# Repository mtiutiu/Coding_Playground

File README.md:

# Coding_Playground

Various coding projects and stuff.

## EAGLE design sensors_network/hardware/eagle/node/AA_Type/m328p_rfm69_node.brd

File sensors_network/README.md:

## MySensors Network 

#### System/RF24 MySensors Network overview

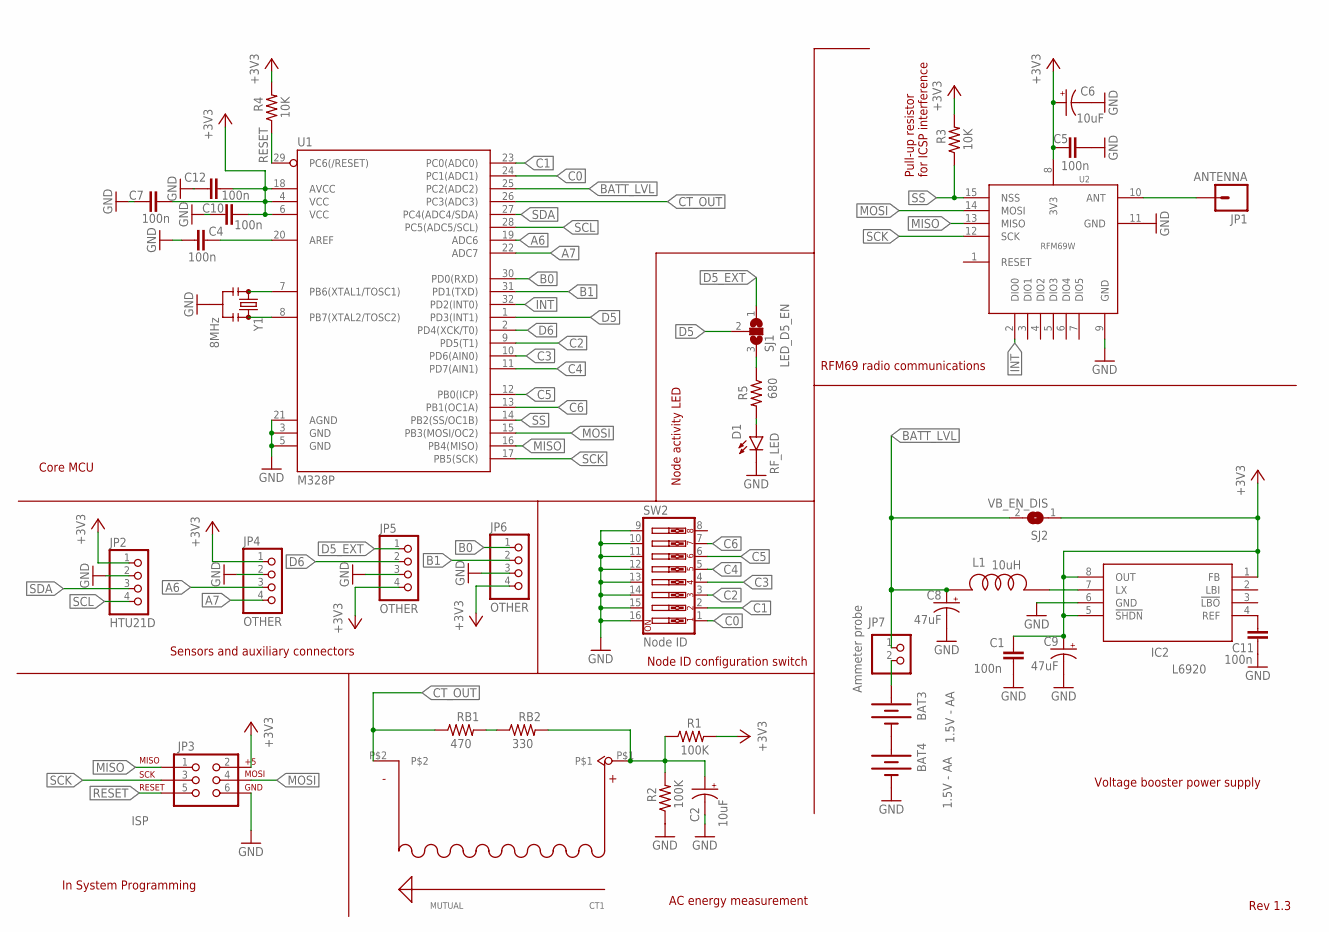
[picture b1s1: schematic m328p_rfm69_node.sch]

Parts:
BAT3, BAT4: 1.5V - AA; BATTERY-AA-KIT
C1, C4, C5, C7, C10, C11, C12: 100n; 0805
C2, C6: 10uF; EIA3528
C8, C9: 47uF; EIA3528
CT1: MUTUAL
D1: RF_LED; LED-0603
IC2: L6920; TSSOP8
JP1: ANTENNA; LUXEON-PAD
JP2: HTU21D; 1X04
JP3: ISP; 2X3-NS
JP4, JP5, JP6: OTHER; 1X04
JP7: Ammeter probe; 1X02
L1: 10uH; DLJ-4018
R1, R2: 100K; 0805
R3, R4: 10K; 0805
R5: 680; 0805
RB1: 470; 0805
RB2: 330; 0805
SJ1: LED_D5_EN; SJ_2
SJ2: VB_EN_DIS; SJ
SW2: Node ID; DIPSWITCH-08-50MIL
U1: M328P; TQFP32-08
U2: RFM69W
Y1: 8MHz; RESONATOR-SMD_MED

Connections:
+3V3: C1.1, C5.1, C6.A (+), C7.2, C9.A (+), C10.2, C12.2, IC2.1 (FB), IC2.5 (!SHDN), IC2.8 (OUT), JP2.1, JP3.2, JP4.1, JP5.4, JP6.4, R1.2, R3.2, R4.2, SJ2.1, U1.4 (VCC), U1.6 (VCC), U1.18 (AVCC), U2.8 (3V3)
A6: JP4.3, U1.19 (ADC6)
A7: JP4.4, U1.22 (ADC7)
B0: JP6.1, U1.30 (PD0(RXD))
B1: JP6.2, U1.31 (PD1(TXD))
BATT_LVL: C8.A (+), JP7.1, L1.P$2 (2), SJ2.2, U1.25 (PC2(ADC2))
C0: SW2.1, U1.24 (PC1(ADC1))
C1: SW2.2, U1.23 (PC0(ADC0))
C2: SW2.3, U1.9 (PD5(T1))
C3: SW2.4, U1.10 (PD6(AIN0))
C4: SW2.5, U1.11 (PD7(AIN1))
C5: SW2.6, U1.12 (PB0(ICP))
C6: SW2.7, U1.13 (PB1(OC1A))
CT_OUT: CT1.P$2, RB1.1, U1.26 (PC3(ADC3))
D5: SJ1.2, U1.1 (PD3(INT1))
D5_EXT: JP5.1, SJ1.1
D6: JP5.2, U1.2 (PD4(XCK/T0))
GND: BAT4.GND@1 (-), C1.2, C2.C (-), C4.1, C5.2, C6.C (-), C7.1, C8.C (-), C9.C (-), C10.1, C11.2, C12.1, D1.C, IC2.6 (GND), JP2.2, JP3.6, JP4.2, JP5.3, JP6.3, R2.1, SW2.9, SW2.10, SW2.11, SW2.12, SW2.13, SW2.14, SW2.15, SW2.16, U1.3 (GND), U1.5 (GND), U1.21 (AGND), U2.9 (GND), U2.11 (GND), Y1.2
INT: U1.32 (PD2(INT0)), U2.2 (DIO0)
MISO: JP3.1, U1.16 (PB4(MISO)), U2.13 (MISO)
MOSI: JP3.4, U1.15 (PB3(MOSI/OC2)), U2.14 (MOSI)
unnamed: IC2.7 (LX), L1.P$1 (1)
unnamed: D1.A, R5.2
unnamed: RB1.2, RB2.1
unnamed: C11.1, IC2.4 (REF)
unnamed: BAT3.PWR@1 (+), JP7.2
unnamed: U1.8 (PB7(XTAL2/TOSC2)), Y1.3
unnamed: BAT3.GND@1 (-), BAT4.PWR@1 (+)
unnamed: U1.7 (PB6(XTAL1/TOSC1)), Y1.1
unnamed: JP1.P$1, U2.10 (ANT)
unnamed: C2.A (+), CT1.P$1, R1.1, R2.2, RB2.2
unnamed: C4.2, U1.20 (AREF)
unnamed: R5.1, SJ1.3
RESET: JP3.5, R4.1, U1.29 (PC6(/RESET))
SCK: JP3.3, U1.17 (PB5(SCK)), U2.12 (SCK)
SCL: JP2.4, U1.28 (PC5(ADC5/SCL))
SDA: JP2.3, U1.27 (PC4(ADC4/SDA))
SS: R3.1, U1.14 (PB2(SS/OC1B)), U2.15 (NSS)

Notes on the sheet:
In System Programming
Sensors and auxiliary connectors
Core MCU
RFM69 radio communications
Voltage booster power supply
AC energy measurement
Pull-up resistor for ICSP interference
Node ID configuration switch
Node activity LED
Rev 1.3

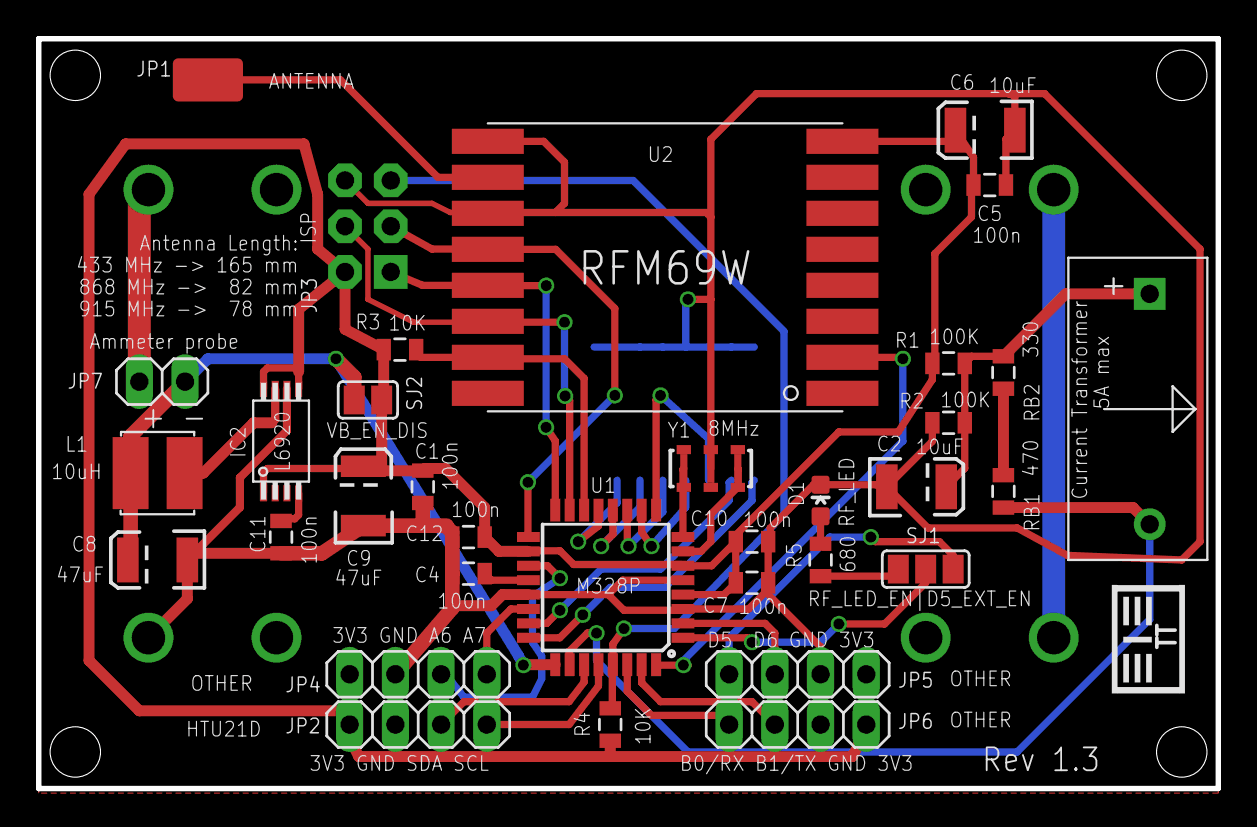
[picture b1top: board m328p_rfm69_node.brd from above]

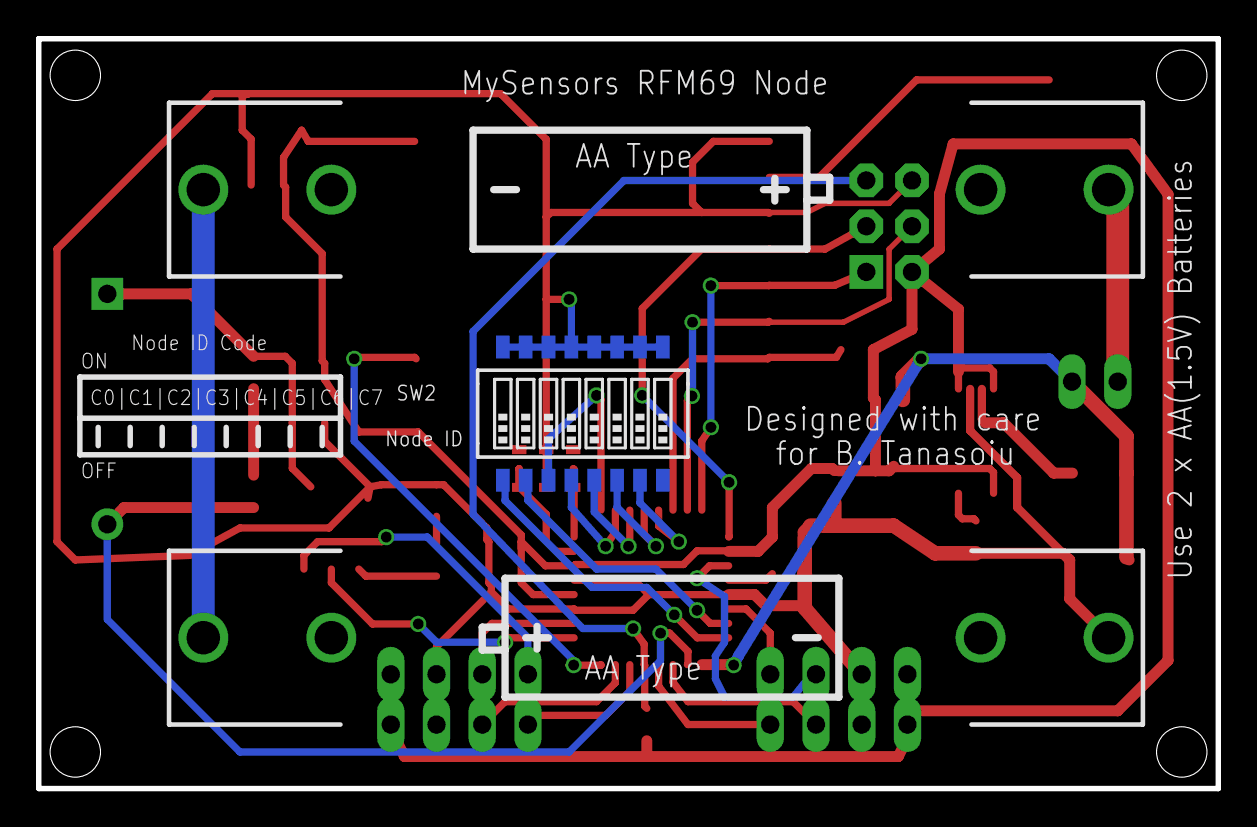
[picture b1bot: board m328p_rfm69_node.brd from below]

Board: 2 copper layers, 65.5 x 41.7 mm, 37 parts (3 on the bottom side), 38 nets.

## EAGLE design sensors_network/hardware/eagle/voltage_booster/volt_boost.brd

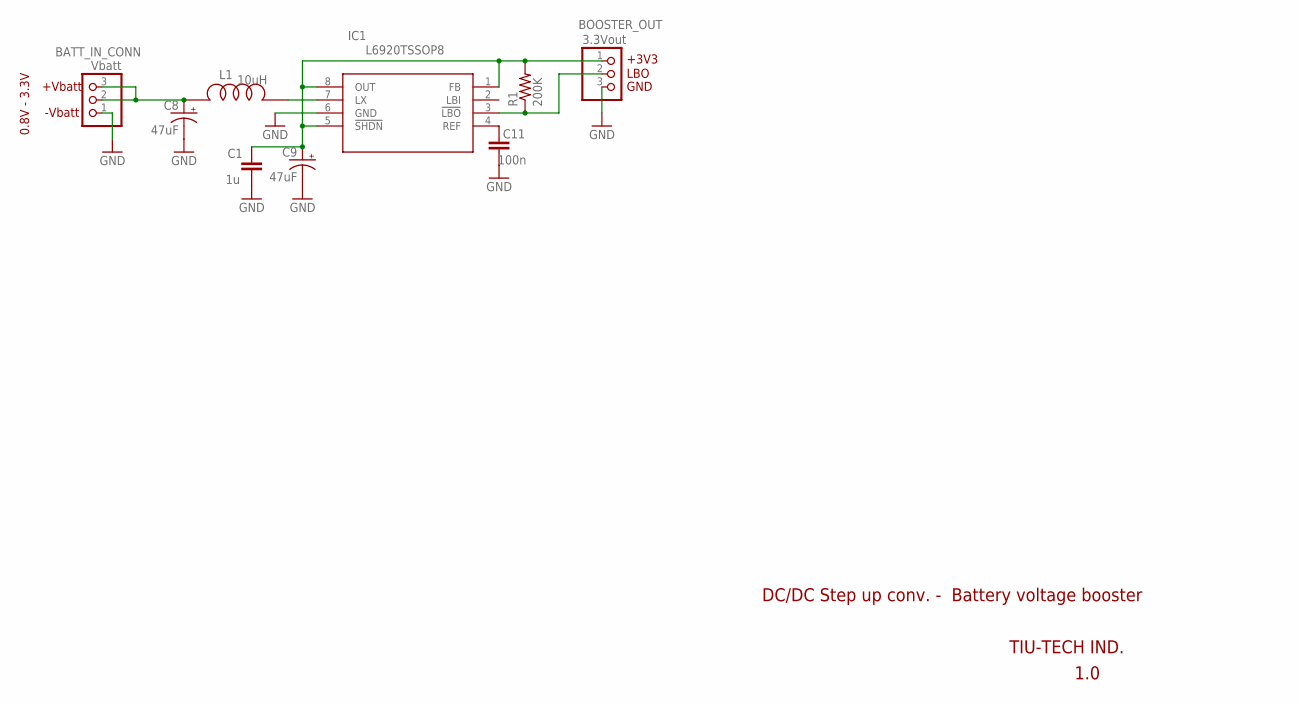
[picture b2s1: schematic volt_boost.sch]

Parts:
BATT_IN_CONN: Vbatt; 1X03
BOOSTER_OUT: 3.3Vout; 1X03
C1: 1u; 0805
C8, C9: 47uF; EIA3528
C11: 100n; 0805
IC1: L6920TSSOP8; TSSOP8
L1: 10uH; DLJ-4018
R1: 200K; 0805

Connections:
+3.3V: BOOSTER_OUT.1, C1.1, C9.A (+), IC1.1 (FB), IC1.5 (!SHDN), IC1.8 (OUT), R1.2
GND: BATT_IN_CONN.1, BOOSTER_OUT.3, C1.2, C8.C (-), C9.C (-), C11.2, IC1.6 (GND)
unnamed: IC1.7 (LX), L1.P$1 (1)
unnamed: BATT_IN_CONN.2, BATT_IN_CONN.3, C8.A (+), L1.P$2 (2)
unnamed: BOOSTER_OUT.2, IC1.3 (!LBO), R1.1
unnamed: C11.1, IC1.4 (REF)

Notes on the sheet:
TIU-TECH IND.
1.0
DC/DC Step up conv. - Battery voltage booster
+Vbatt
-Vbatt
+3V3
LBO
GND
0.8V - 3.3V

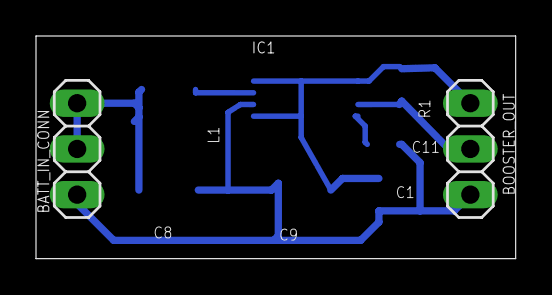
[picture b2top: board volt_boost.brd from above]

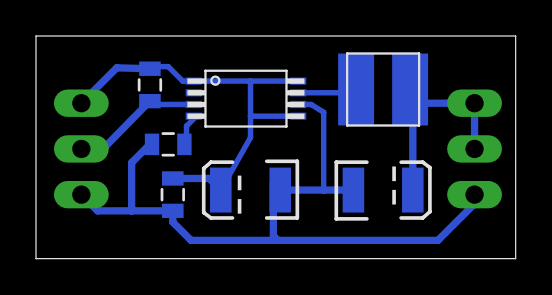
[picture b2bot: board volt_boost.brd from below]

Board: 2 copper layers, 26.6 x 12.4 mm, 9 parts (7 on the bottom side), 6 nets.

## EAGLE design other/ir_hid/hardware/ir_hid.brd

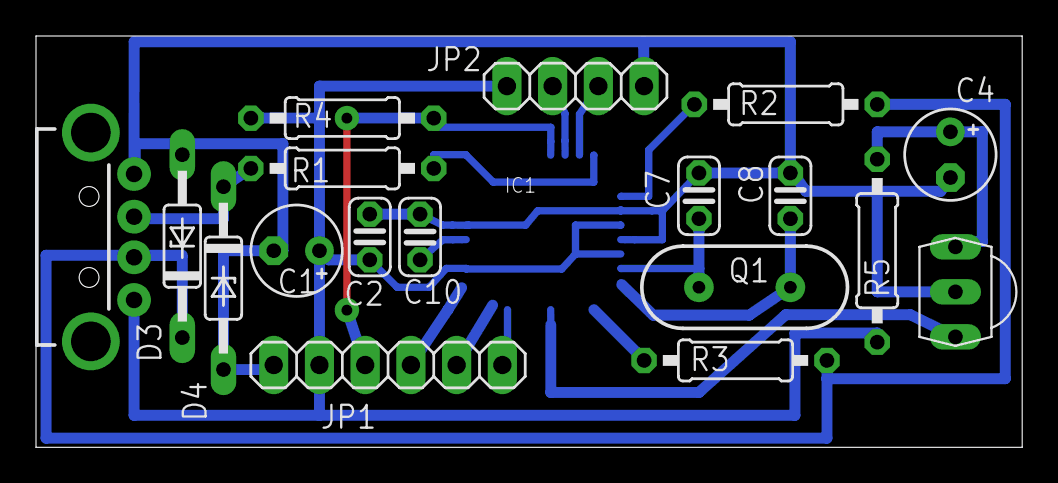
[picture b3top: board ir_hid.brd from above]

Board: 2 copper layers, 54.8 x 22.9 mm, 19 parts (1 on the bottom side), 16 nets.

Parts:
C1, C4: 4u7/16V; E2,5-5
C2, C10: 100nF; C025-024X044
C7, C8: 22pF; C025-024X044
D3, D4: ZPD-3V6; DO35Z10
IC1: MEGA8-16AU(8AU); TQFP32-08
JP1: ISP; 1X06
JP2: UART; 1X04
Q1: 12MHz; HC49US
R1, R2: 68; 0207/10
R3: 2K2; 0207/10
R4: 10K; 0207/10
R5: 100; 0207/10
U$1: TSOP4838; TSOP18XX
X1: USBA-LP; USB-A-H

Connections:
5V: C1.+, C2.1, IC1.4, IC1.6, IC1.18, JP1.5, JP2.1, R4.1, R5.1, X1.VBUS
GND: C1.-, C2.2, C4.-, C7.2, C8.2, C10.1, D3.A, D4.A, IC1.3, IC1.5, IC1.21, JP1.6, JP2.4, U$1.GND, X1.GND
unnamed: IC1.32, R1.1
unnamed: IC1.9, R3.1
unnamed: IC1.2, R2.1
unnamed: D4.C, R1.2, X1.D+
unnamed: C10.2, IC1.20
unnamed: D3.C, R2.2, R3.2, X1.D-
unnamed: C7.1, IC1.7, Q1.1
unnamed: C8.1, IC1.8, Q1.2
unnamed: IC1.29, JP1.4, R4.2
unnamed: C4.+, R5.2, U$1.VCC
unnamed: IC1.30, JP2.2
unnamed: IC1.15, JP1.1
unnamed: IC1.31, JP2.3
unnamed: IC1.12, U$1.OUT

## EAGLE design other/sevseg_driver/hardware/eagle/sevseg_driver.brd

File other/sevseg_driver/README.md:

# sevseg_driver
Seven segment display testing with shift registers

# demo
https://youtu.be/TXsOFp60iu4

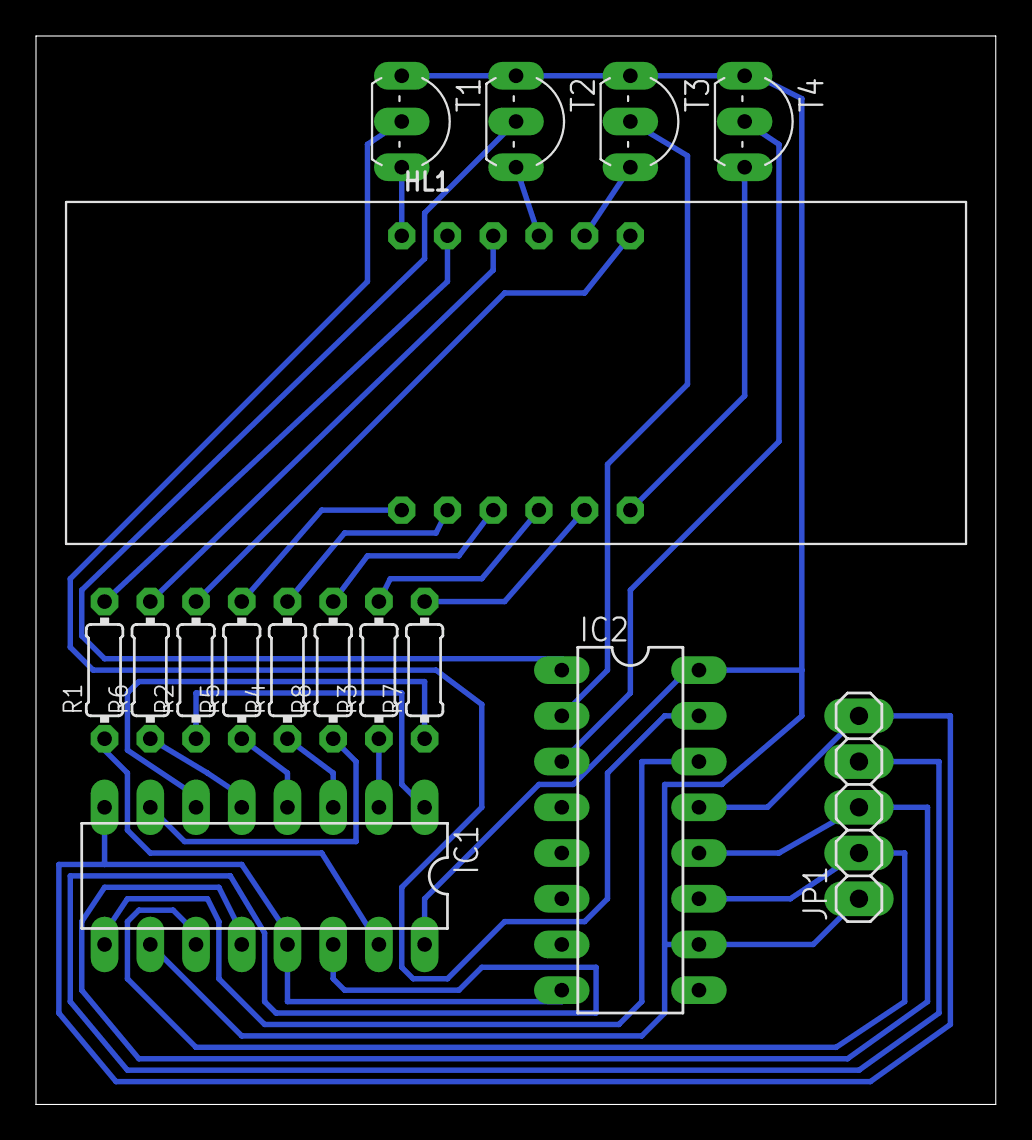
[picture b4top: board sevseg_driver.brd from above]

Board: 2 copper layers, 53.3 x 59.4 mm, 16 parts (0 on the bottom side), 30 nets.

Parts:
HL1: A-564E; C/A-564
IC1, IC2: 74HC595N; DIL16
JP1: MCU; 1X05
R1, R2, R3, R4, R5, R6, R7, R8: 220; 0204/7
T1, T2, T3, T4: BC338; TO92-EBC

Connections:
GND: IC1.8, IC1.13, IC2.8, IC2.13, JP1.5
unnamed: IC1.15, R1.1
unnamed: HL1.3, R8.2
unnamed: HL1.11, R1.2
unnamed: IC1.1, R2.1
unnamed: HL1.7, R2.2
unnamed: HL1.4, R3.2
unnamed: IC1.2, R3.1
unnamed: IC1.3, R4.1
unnamed: IC1.9, IC2.14
unnamed: HL1.12, T1.E
unnamed: HL1.9, T2.E
unnamed: HL1.8, T3.E
unnamed: HL1.6, T4.E
unnamed: IC1.14, JP1.4
unnamed: HL1.2, R4.2
unnamed: HL1.1, R5.2
unnamed: IC1.4, R5.1
unnamed: IC1.5, R6.1
unnamed: HL1.10, R6.2
unnamed: HL1.5, R7.2
unnamed: IC1.6, R7.1
unnamed: IC1.7, R8.1
unnamed: IC2.15, T1.B
unnamed: IC2.1, T2.B
unnamed: IC2.2, T3.B
unnamed: IC2.3, T4.B
unnamed: IC1.12, IC2.12, JP1.3
unnamed: IC1.11, IC2.11, JP1.2
VCC: IC1.10, IC1.16, IC2.10, IC2.16, JP1.1, T1.C, T2.C, T3.C, T4.C

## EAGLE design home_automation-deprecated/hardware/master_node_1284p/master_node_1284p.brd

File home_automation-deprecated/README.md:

Home Automation Solution. Currently only light nodes are implemented.

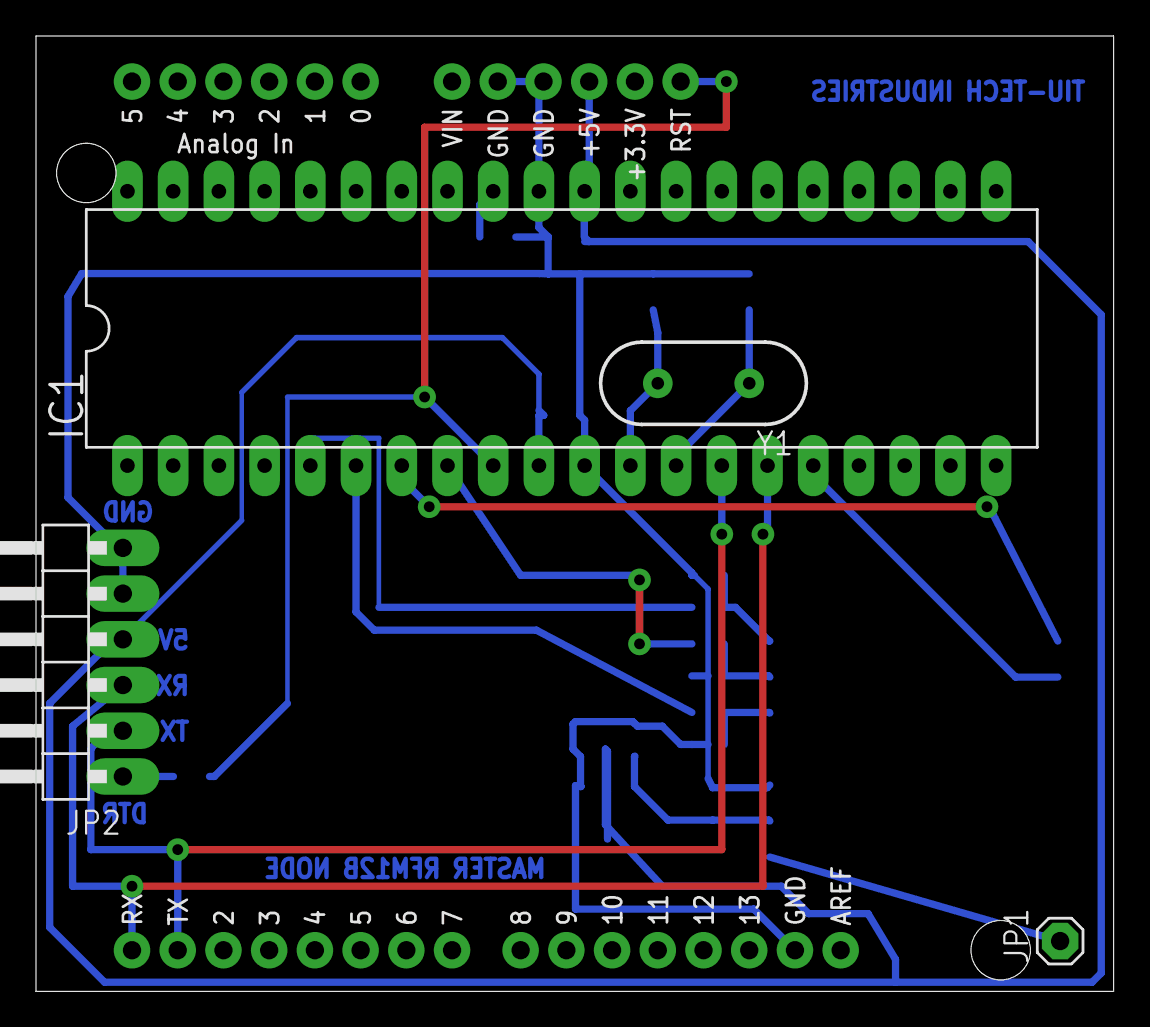
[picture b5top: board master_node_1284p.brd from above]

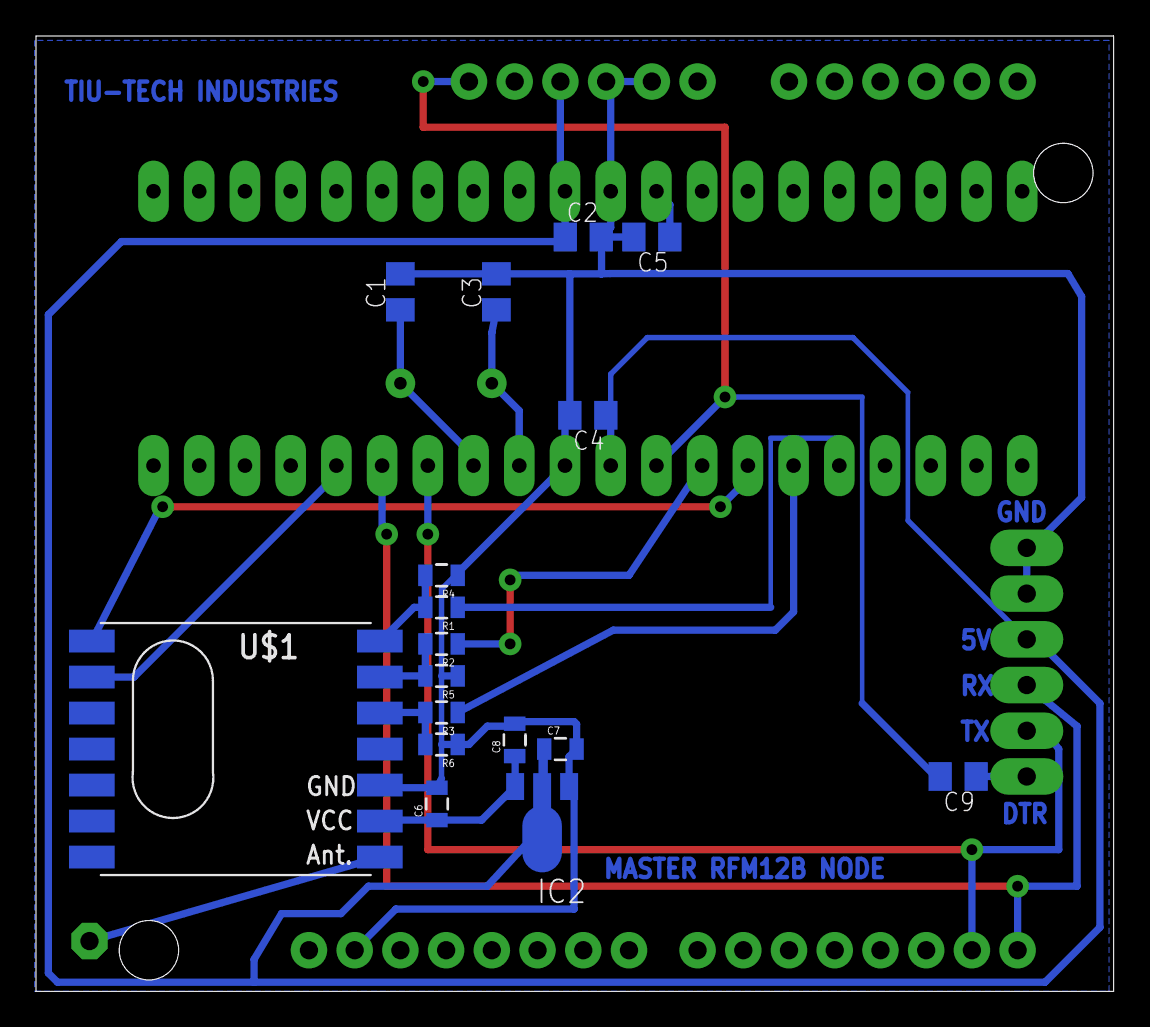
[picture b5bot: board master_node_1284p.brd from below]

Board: 2 copper layers, 59.9 x 53.1 mm, 22 parts (17 on the bottom side), 19 nets.

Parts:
C1, C3: 22p; C0805K
C2, C4, C5, C9: 100n; C0805K
C6, C7, C8: 1u; 0805
IC1: ATMEGA644-20PU; DIL40
IC2: MCP1703-3V3; MCP1703-SOT89
JP1: ANT; 1X01
JP2: PROGRAMMER; 1X06/90
R1, R2, R3: 4K7; 0805
R4, R5, R6: 10K; 0805
U1: ARDUINO_SHIELDLABEL; DUEMILANOVE_SHIELD
U$1: RFM12B
Y1: 16MHz; HC49US

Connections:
5VCC: C2.1, C4.1, C7.1, IC1.10, IC1.30, IC2.VIN1, IC2.VIN2, JP2.4, U1.5V
+3V3: C6.1, C8.1, IC2.VOUT, U$1.VDD
DTR: C9.1, JP2.1
GND: C1.2, C2.2, C3.2, C4.2, C5.2, C6.2, C7.2, C8.2, IC1.11, IC1.31, IC2.GND, JP2.5, JP2.6, R4.1, R5.1, R6.1, U1.GND@0, U1.GND@1, U1.GND@2, U$1.GND
IRQ: IC1.16, U$1.IRQ
MISO: IC1.7, U$1.SDO
MOSI: IC1.6, R3.1
unnamed: JP1.1, U$1.ANT
unnamed: C5.1, IC1.32
unnamed: R3.2, R6.2, U$1.SDI
unnamed: R2.2, R5.2, U$1.SCK
unnamed: R1.2, R4.2, U$1.SEL
RESET: C9.2, IC1.9, U1.RES
RX: IC1.15, JP2.3, U1.RX
SCK: IC1.8, R2.1
SS: IC1.5, R1.1
TX: IC1.14, JP2.2, U1.TX
XTAL1: C1.1, IC1.13, Y1.1
XTAL2: C3.1, IC1.12, Y1.2

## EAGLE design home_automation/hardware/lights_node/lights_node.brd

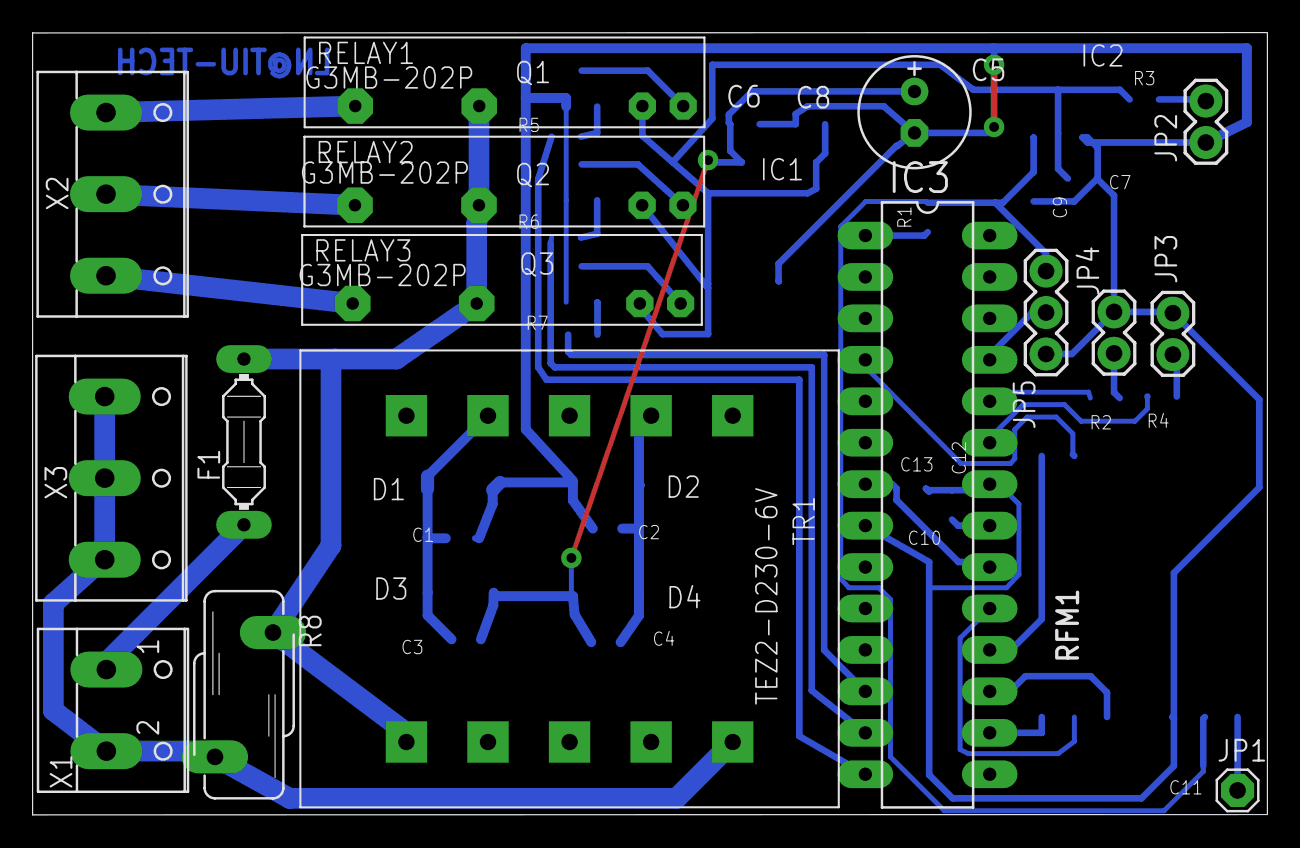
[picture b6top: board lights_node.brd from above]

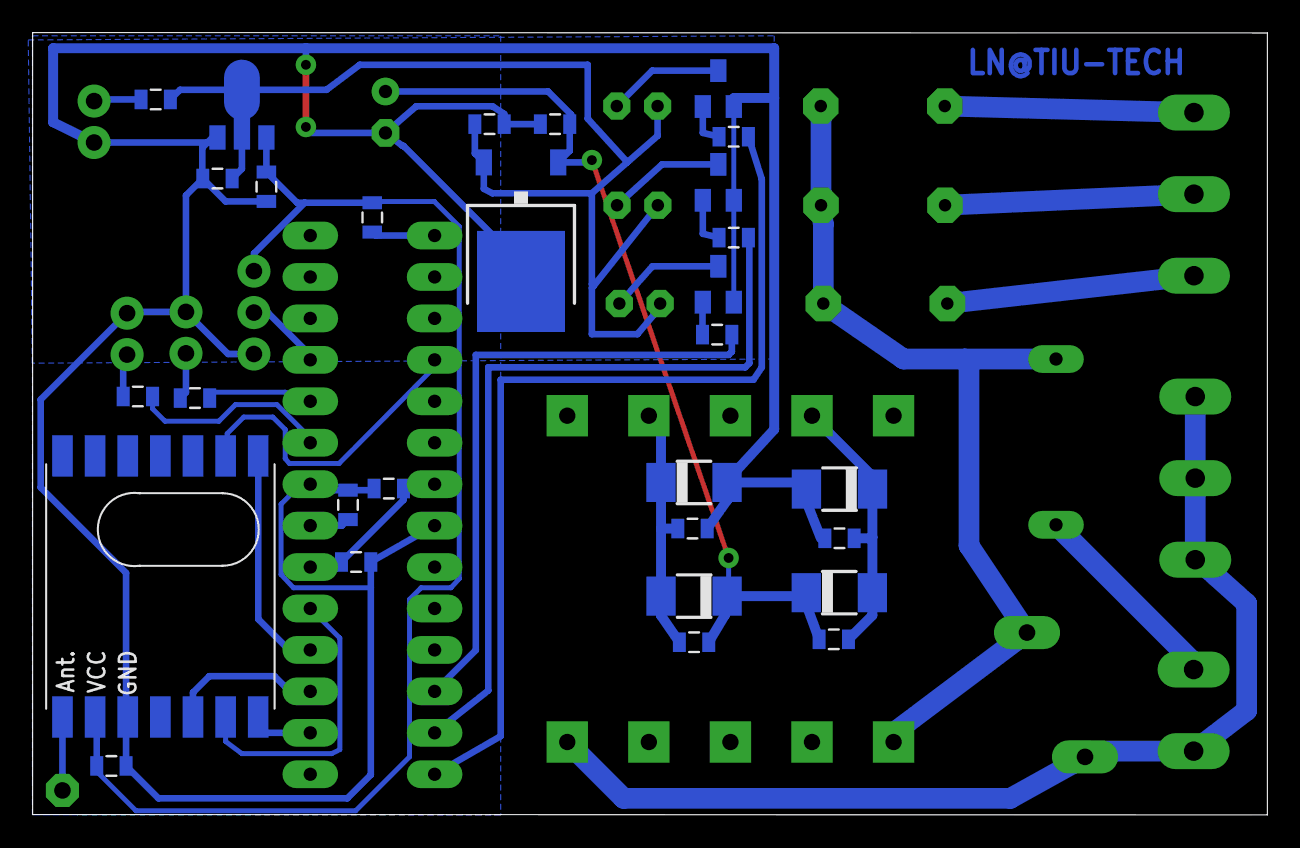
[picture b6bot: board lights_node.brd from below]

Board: 2 copper layers, 75.7 x 47.9 mm, 45 parts (29 on the bottom side), 35 nets.

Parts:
C1, C2, C3, C4: 0.1u/63V; 0805
C5: 470u/16V; E2,5-7
C6, C7, C8, C9, C11: 1u; 0805
C10, C12, C13: 0.1u; 0805
D1, D2, D3, D4: M7; DO-214AC
F1: 240Vac/3.15A; PICOFUSE
IC1: 7805DT; TO252
IC2: MCP1703-3V3; MCP1703-SOT89
IC3: ATMEGA48/88/168-PU; DIL28-3
JP1: ANT; 1X01
JP2, JP3, JP4: M02PTH; 1X02
JP5: IR SENSOR; 1X03
Q1, Q2, Q3: BC846; SOT23-BEC
R1: 10K; 0805
R2, R4: 270; 0805
R3: 470; 0805
R5, R6, R7: 36K; 0805
R8: S10K300
RELAY1, RELAY2, RELAY3: G3MB-202P
RFM1: RFM12B
TR1: TEZ2-D230-6V; TEZ1.5-PKG
X1: 230Vac; W237-102
X2: L-H; W237-103
X3: L-N; W237-103

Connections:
+3V3: C9.1, C10.1, C11.1, C13.2, IC2.VOUT, IC3.7, IC3.20, JP5.1, R1.1, RFM1.VDD
+5V: C7.1, C8.1, IC1.2, IC2.VIN1, IC2.VIN2, R3.1, RELAY1.IN+, RELAY2.IN+, RELAY3.IN+
AGND: R8.2, TR1.P1, X1.2, X3.1, X3.2, X3.3
GND: C1.1, C2.1, C5.-, C6.2, C7.2, C8.2, C9.2, C10.2, C11.2, C12.2, C13.1, D1.A, D2.A, IC1.3, IC2.GND, IC3.8, IC3.22, JP2.1, JP3.2, JP4.1, JP5.3, Q1.E, Q2.E, Q3.E, RFM1.GND
IRQ: IC3.4, RFM1.IRQ
IR_DATA: IC3.25, JP5.2
IR_LED: IC3.24, R2.1
MISO: IC3.18, RFM1.SDO
MOSI: IC3.17, RFM1.SDI
unnamed: F1.2, R8.1, RELAY1.K1, RELAY2.K1, RELAY3.K1, TR1.P5
unnamed: RELAY1.K2, X2.1
unnamed: RELAY2.K2, X2.2
unnamed: RELAY3.K2, X2.3
unnamed: Q1.C, RELAY1.IN-
unnamed: Q1.B, R5.1
unnamed: Q2.C, RELAY2.IN-
unnamed: JP2.2, R3.2
unnamed: JP4.2, R2.2
unnamed: C1.2, C3.1, D1.C, D3.A, TR1.S7
unnamed: C2.2, C4.1, D2.C, D4.A, TR1.S9
unnamed: JP3.1, R4.2
unnamed: Q2.B, R6.1
unnamed: Q3.B, R7.1
unnamed: C12.1, IC3.21
unnamed: JP1.1, RFM1.ANT
unnamed: Q3.C, RELAY3.IN-
unnamed: F1.1, X1.1
RELAY1_CMD: IC3.14, R5.2
RELAY2_CMD: IC3.13, R6.2
RELAY3_CMD: IC3.12, R7.2
RESET: IC3.1, R1.2
RF_LED: IC3.23, R4.1
SCK: IC3.19, RFM1.SCK
SS: IC3.16, RFM1.SEL
VRAW: C3.2, C4.2, C5.+, C6.1, D3.C, D4.C, IC1.1

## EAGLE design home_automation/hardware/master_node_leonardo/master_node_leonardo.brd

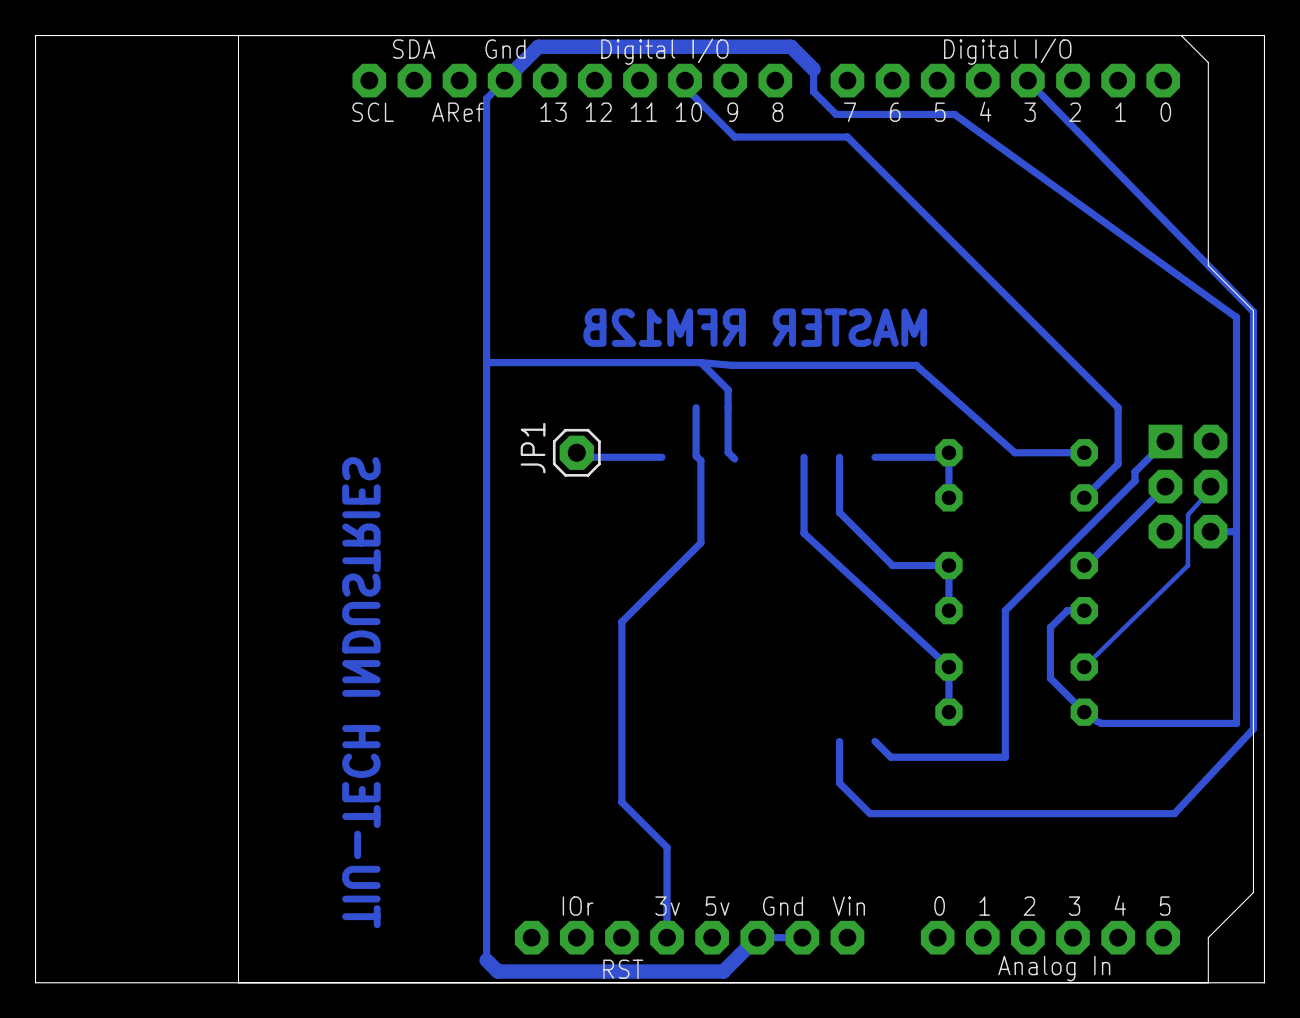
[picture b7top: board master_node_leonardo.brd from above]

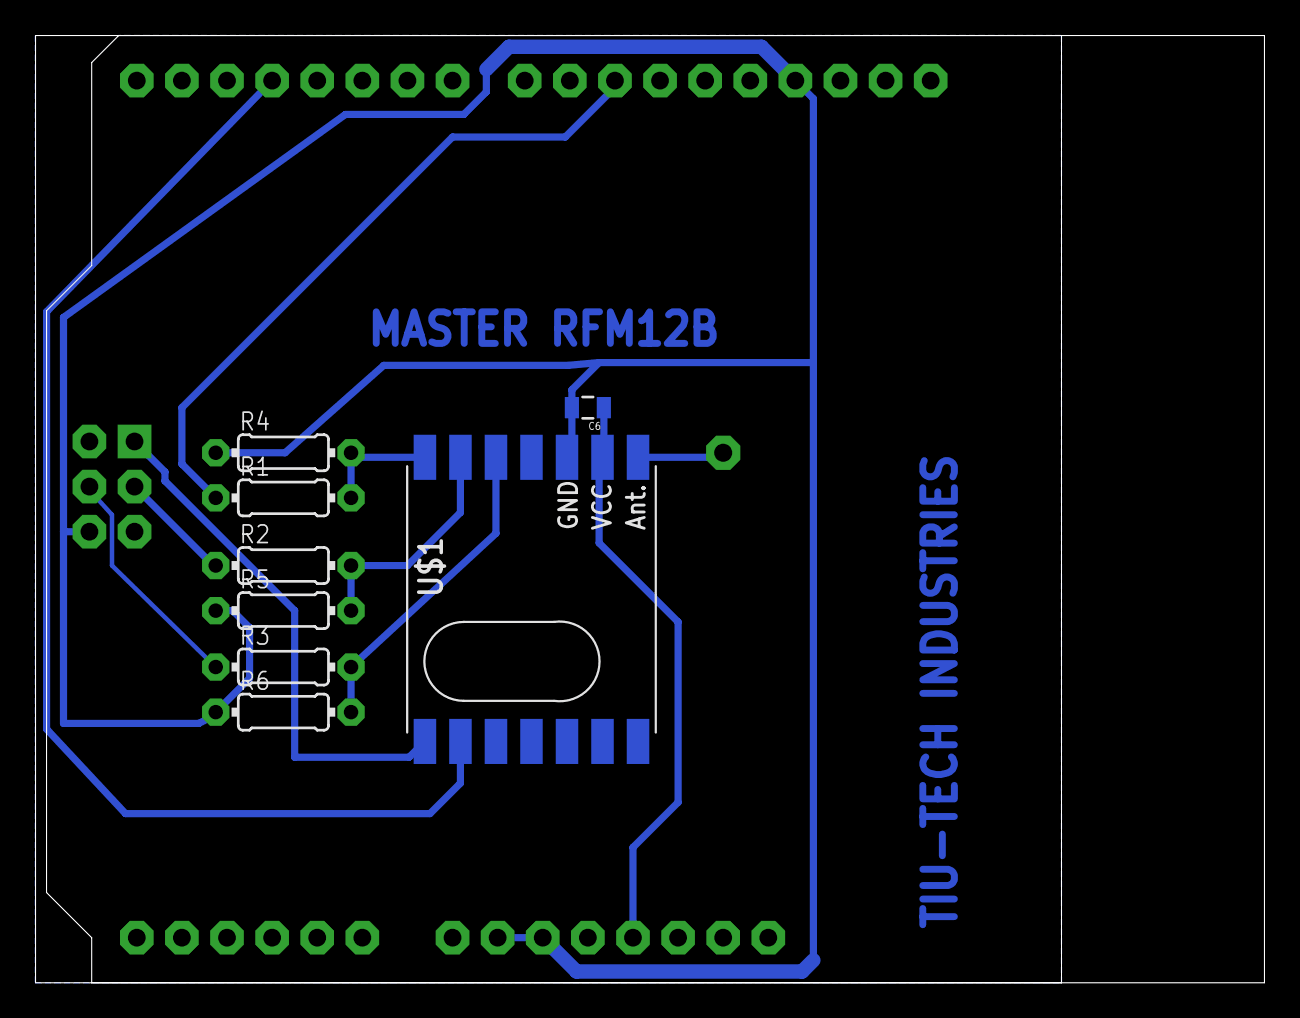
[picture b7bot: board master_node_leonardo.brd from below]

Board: 2 copper layers, 69.2 x 53.3 mm, 10 parts (8 on the bottom side), 11 nets.

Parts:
C6: 1u; 0805
JP1: ANT; 1X01
R1, R2, R3: 4K7; 0204/7
R4, R5, R6: 10K; 0204/7
U$1: RFM12B
U$2: ARDUINO_R3_ICSP; ARDUINOR3_ICSP

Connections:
+3V3: C6.1, U$1.VDD, U$2.3V
GND: C6.2, R4.1, R5.1, R6.1, U$1.GND, U$2.GND, U$2.GND@1, U$2.GND@2, U$2.GND@3
IRQ: U$1.IRQ, U$2.D3
MISO: U$1.SDO, U$2.MISO
MOSI: R3.1, U$2.MOSI
unnamed: JP1.1, U$1.ANT
unnamed: R3.2, R6.2, U$1.SDI
unnamed: R2.2, R5.2, U$1.SCK
unnamed: R1.2, R4.2, U$1.SEL
SCK: R2.1, U$2.SCK
SS: R1.1, U$2.D10

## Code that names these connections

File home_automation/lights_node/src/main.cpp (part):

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const uint8_t NETWORK_ID = 99;       //the network ID we are on

const uint8_t MAX_CHANNELS = 3;
const uint8_t RELAY1_CMD_PIN = 6;
const uint8_t RELAY2_CMD_PIN = 7;
const uint8_t RELAY3_CMD_PIN = 8;
const uint8_t CHANNELS_RELAY_PINS[] = {RELAY1_CMD_PIN, RELAY2_CMD_PIN, RELAY3_CMD_PIN};

const uint8_t ON = HIGH;
const uint8_t OFF = LOW;
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
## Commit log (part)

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2017-03-10 update speed for upload on serial gw
2017-03-13 reduced tx retries interval for non-battery powered nodes
2017-03-14 [LivoloLightsNode] increased a little bit touch threshold time
2017-03-16 [mysensors heater node] updated platformio.ini for new board
2017-03-16 [mysensors heater/livolo nodes] added info regarding initial MCU fuse setup
2017-03-16 added required bootloader files
2017-03-16 [mysensors heater node] updated pin definitions
2017-03-27 [LedStripActuatorNode] added ota bootloader specific to mini R board
2017-03-29 disabled heartbeat/presentation regular sending
2017-03-29 [HeaterNode] changed node type to S_HEATER
2017-04-03 [mysensors][SerialGateway] changed network discovery interval to 24h
2017-04-28 [LedStripActuatorNode] changed pins according to new hardware, added bootloader
2017-05-10 added WS28xxControllerNode node
2017-05-10 replaced millis with hwMillis for portability and added ws28xx controller initial logic
2017-05-10 [mysensors][WS28xxControllerNode] added save/load rgb led strip settings helper functions
2017-05-10 [mysensors][WS28xxControllerNode] added binary sensor for on/off states
2017-05-11 [mysensors][WS28xxControllerNode] updated libraries for more efficient RAM/Flash usage and refactored sketch
2017-05-11 [mysensors][WS28xxControllerNode] added reply to controller for each setting
2017-05-11 [mysensors][WS28xxControllerNode] various bugs fixing
2017-05-12 [mysensors][WS28xxControllerNode] mapped more appropriate vars for controller actions
2017-05-15 [mysensors][WS28xxControllerNode] sketch refactorings - removed led strip status variable as ws2812fx libs already maintains state internally - used start/stop/isRunning methods instead
2017-05-16 [mysensors][WS28xxControllerNode] sketch refactorings
2017-06-01 adeed mysensors 2.2.0-beta core
2017-06-09 changed RF69_868MHZ to RFM69_868MHZ
2017-06-09 increased sketch version to 2.2
2017-06-14 [mysensors] switched to new rfm69 driver
2017-06-20 [mysensors] refactored sketches
2017-06-20 added editorconfig
2017-06-20 editorconfig - tab 2 spaces
2017-07-05 livolo lights node nrf5 support
2017-07-05 added repeater node feature for livolo nodes
2017-07-06 removed wait from livolo lights sketch
2017-07-26 LivoloLightsNode - refactorings for mtch105
2017-08-08 MySensors LivoloLightsNode - node ids class changed to 1xx, fixed relays channel
2017-08-09 MySensors LivoloLightsNode - set node metadata functionality
2017-08-09 MySensors sketches - fixed memset
2017-08-10 livolo sketch updates
2017-08-10 WS28xxControllerNode refactorings, added bootloader
2017-09-27 updated mysensors core and livolo switch sketch
2017-10-03 livolo ble code
2017-10-04 livolo ble sketch refactorings
2017-10-04 Livolo ble sketch - more descriptive comments for the configuration section
2017-10-04 Livolo ble sketch - more code comments
2017-10-05 livolo ble refactorings
2017-10-12 livolo ble sketch and central refactorings
2017-10-16 livolo ble - python central refactorings
2017-10-31 livolo ble central refactorings
2017-10-31 livolo ble controller - added mqtt testing
2017-11-01 ble central - mqtt integration 1st pass
2017-11-01 ble central - mqtt integration 2nd pass
2017-11-01 ble central - mqtt integration 3rd pass
2017-11-03 added ble stats panel
2017-11-04 livolo ble central - power on automatically adapter if not powered
2017-11-05 ble central - refactorings
2017-11-06 ble central - added stats panel mqtt reconnection feature, sijax support
2017-11-06 ble central - fixed mqtt topics registration and data sending to mycontroller
2017-11-06 Update livolo_ble.py
    hci0 instead of hci1
2017-11-07 ble central - fixes and fixes
2017-11-07 ble central - restructuring
2017-11-07 ble central - added system stats panel
2017-11-07 ble central stats panel refactorings
2017-11-08 ble central - extra deps readme, other fixes
2017-11-08 ble central - service check fix for better portability
2017-11-08 ble central -other fixes
2017-11-08 ble central - services refactorings
2017-11-08 ble central - fixes and fixes - don't use threads when not really needed cause they are tricky to work with
2017-11-08 ble central - multiple instances
2017-11-09 ble central refactorings - livolo ble use multiple instances
2017-11-09 ble central - add ble device alias
2017-11-10 ble central - small refactorings
2017-11-10 ble central - stability issues fixes
2017-11-10 ble central - livolo ble service - don't block in init if mqtt not available
2017-11-10 livolo ble central - don't do any mqtt in/out when device is not connected over bluetooth
2017-11-10 ble central - systemd services configs - fix username for raspbian images
2017-11-13 ble central - add mqtt msg retention option
2017-11-13 ble central - mqtt msg retention - true
2017-11-13 ble central - added services tab, refactorings
2017-11-13 ble central - unify configs
2017-11-13 ble central - ble stats panel refactorings
2017-11-14 ble central - added settings page
2017-11-14 ble central - settings page finish up, lots of refactorings
2017-11-14 ble central - web config panel refactorings
2017-11-14 ble central - web panel refactorings
2017-11-15 ble central - enable mqtt msgs retention by default
2017-11-15 ble central - add mqtt auth for livolo ble central service
2017-11-15 ble central - report livolo lights state at regular intervals
2017-11-16 ble central - refact
2017-11-17 ble central - improved mysensors helper
2017-11-17 ble central - improved mysensors helper - fixed node id for presenting node
2017-11-27 ble central - battery level reporting added and some minor refactorings regarding main app threads
2017-11-27 ble central - battery level reporting interval set to 5mins
2017-11-28 ble central - removed webpanel dependency on mqtt and use d-bus to fetch ble stats
2017-11-29 ble central - livolo_ble - refactorings
2017-11-29 ble central - webpanel - added tabs loader animation
2017-12-04 ble central - web panel read cpu temperature in a more portable way
2017-12-15 added wemos mini testing project
2017-12-16 wemos test - added mqtt
2017-12-19 wemos node - added mysensors mqtt support
2017-12-20 wemos mqtt - added mysensors config data
2017-12-22 wemos mqtt - refactorings
2018-01-09 wemos mqtt -refactorings
2018-01-10 mys ble - decoupled mqtt logic - moved to mysensors helper, wemos mqtt - use a reference for message data instead of copying to stack
2018-01-12 reorganized sources tree
2018-01-12 esp8266 mqtt-mysensors integration sketches refactorings
2018-01-13 esp8266 mqtt ws812fx refactorings
2018-01-14 esp8266 mqtt - ws2812fx refactorings
2018-01-14 esp8266 mqtt - ws2812fx fixed led strip init sequence
2018-01-15 esp8266 ws2812fx - added configurable number of leds option, code refactorings
2018-01-15 esp8266 mysensors - added esp restart instead of reset as it's safer
2018-01-15 esp8266 folder structure
2018-01-16 esp8266 ws2812fx controller - remap pins for wemos d1 board
2018-01-16 esp8266 ws2812fx - added led strip on/off button
2018-01-16 esp8266 ws2812fx - fixed led strip ctrl button debounce
2018-01-16 esp8266 ws2812fx - refactorings
2018-01-18 esp8266 ws2812fx - switched to fastled lib and added wrapper
2018-01-22 esp8266 mqtt projects - refactorings
2018-01-25 esp8266 refactorings
2018-01-25 esp8266 refactorings - default broker ip
2018-01-26 livolo ble central - added new gatt linux patch file
2018-02-05 livolo ble project structure refactorings
2018-02-07 esp8266 mqtt refactorings
2018-02-12 wifi manager minor fixes ported from main development
2018-02-13 esp8266 sketches fixes
2018-03-10 mysensors 2.2.0 stable release
2018-03-10 mys temp sensor refactorings
2018-05-23 fixed (hopefully) the debouncing filter for livolo switches touch sensor
2018-05-23 livolo lights node - avoid delay functions
2018-05-24 livolo eu switch nrf5 refactorings
2018-06-07 livolo eu switch - added nrf52 support
2018-06-07 livolo eu switch - refactored platformio.ini and pin defs
2018-06-07 livolo eu switch - removed unnecessary warnings
2018-06-11 caca
2018-06-15 livolo firmware - added eeprom support
2018-07-09 esp8266 - added new ws2812fx node
2018-07-18 updated livolo services deps
2018-07-24 livolo central ble app refactorings
2018-07-24 livolo central ble add logrotate for app logs
2018-07-24 livolo central ble webpanel visual refactorings
2018-07-25 livolo ble project structure and psoc ble projects added
2018-07-25 livolo ble project structure
2018-07-31 esp8266 ws2812fx node enhancements
2018-08-01 esp8266 ws2812 updates
2018-08-03 esp8266 switch to makuna neopixel bus great library
2018-08-03 esp8266 libs update, refactorings
2018-08-04 esp8266 mqtt - switched to wifimanager again
2018-09-03 esp mys refactorings
2018-09-03 esp mys port conflict fix
2018-09-07 esp8266 mys refactorings
2018-09-07 remove debug assertions for release targets
2018-09-12 esp mys dir structure refactorings
2018-09-22 wifimanager master code
2018-10-01 livolo ble central fixes/updates
2018-12-02 refactorings
2019-01-10 moved to async libs for esp8266
2019-02-26 added toys project
2019-02-28 bug fixes
2019-04-08 added initial project files for my_home
2019-04-08 sprinkler sketch refactorings
2019-04-09 sprinkler ref
2019-05-03 sprinkler wifi
2019-08-05 updated gitignore
2019-09-03 spr code ref
2019-09-04 spr ref
2019-09-20 added mys custom temp node
2019-09-24 Rename livolo.js to livolo_two_ch.js
2019-10-21 mesh lighting initial commit
2019-10-23 added newt code
2019-10-24 removed repos as it's not required
2019-10-24 holyiot bsp, ref targets
2019-10-24 holyiot module doesn't have external xtal
2019-10-24 added option to disable OOB at build time
2019-10-30 add publisher
2019-11-03 fix length
2019-11-07 nrf52840 custom bsp
2020-01-20 zephyr sketch ref
2020-01-21 code ref
2020-01-23 fixes
2020-01-28 zephyr mesh-onoff project - switch to pio
2020-03-12 Bump psutil in /sensors_network/project/LivoloLightsNode/central
    Bumps [psutil](https://github.com/giampaolo/psutil) from 3.4.2 to 5.6.6.
    - [Release notes](https://github.com/giampaolo/psutil/releases)
    - [Changelog](https://github.com/giampaolo/psutil/blob/master/HISTORY.rst)
    - [Commits](https://github.com/giampaolo/psutil/compare/release-3.4.2...release-5.6.6)
2020-03-27 added capsense project for 1 channel module
2020-03-30 touch switch mesh fix leds state function
2020-03-31 update capsense project
2020-03-31 fixed ts issue for 2ch
2020-03-31 fix ifdef ending
2020-04-08 add v_sense feature control at compile time
2020-04-10 fixed missing semicolon
2020-04-13 newt code cleanup/refactoring
2020-04-16 reverted to mynewt nimble 1.2.0 as things seem to be screwed up for bluetooth mesh networking in the newer version (1.3.0)
2020-04-16 updated next id
2020-04-23 light mesh networking - bugfixes
2020-04-24 update with last node UUID
2020-09-17 mys soil sns
2021-01-04 custom switch board zephyr code - use platformio from now on
2021-02-13 use lowpowerlab rfm69 lib, added custom MySensor wrapper
2021-02-23 mys node ref
2021-02-24 added mesh reset functionality
2021-03-03 re-organize stuff
2021-03-03 Bump psutil in /home_automation/actuators/LivoloLightsNode/central
    Bumps [psutil](https://github.com/giampaolo/psutil) from 3.4.2 to 5.6.6.
    - [Release notes](https://github.com/giampaolo/psutil/releases)
    - [Changelog](https://github.com/giampaolo/psutil/blob/master/HISTORY.rst)
    - [Commits](https://github.com/giampaolo/psutil/compare/release-3.4.2...release-5.6.6)
2021-03-03 Bump flask in /home_automation/actuators/LivoloLightsNode/central
    Bumps [flask](https://github.com/pallets/flask) from 0.12.3 to 1.0.
    - [Release notes](https://github.com/pallets/flask/releases)
    - [Changelog](https://github.com/pallets/flask/blob/master/CHANGES.rst)
    - [Commits](https://github.com/pallets/flask/compare/0.12.3...1.0)
2021-12-10 zephyr prj updates
2021-12-28 lights node zephyr rtos refactoring
2021-12-31 enhance build scripts for zephyr
2022-02-25 updated .gitignore
2022-10-01 mynewt-1.10.0 migration
2022-10-03 updated zephyr rtos mesh lights project to v3.1.0
2022-10-19 refactor build scripts for zephyr

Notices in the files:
parts and their libraries:
SparkFun-Resistors: Licensing: CC v3.0 Share-Alike You are welcome to use this library for commercial purposes.
led-seg: 2009 Draw by Ivan A-R. License CC-BY-SA 3.0
SparkFun-Resistors: Licensing: Creative Commons ShareAlike 4.0 International - https://creativecommons.org/licenses/by-sa/4.0
